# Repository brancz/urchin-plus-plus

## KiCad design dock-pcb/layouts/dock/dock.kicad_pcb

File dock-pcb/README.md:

# dock-pcb

atopile project for the dock board (phase 7), built by the same pipeline as `hardware/`: `scripts/ato_build.sh dock-pcb`.

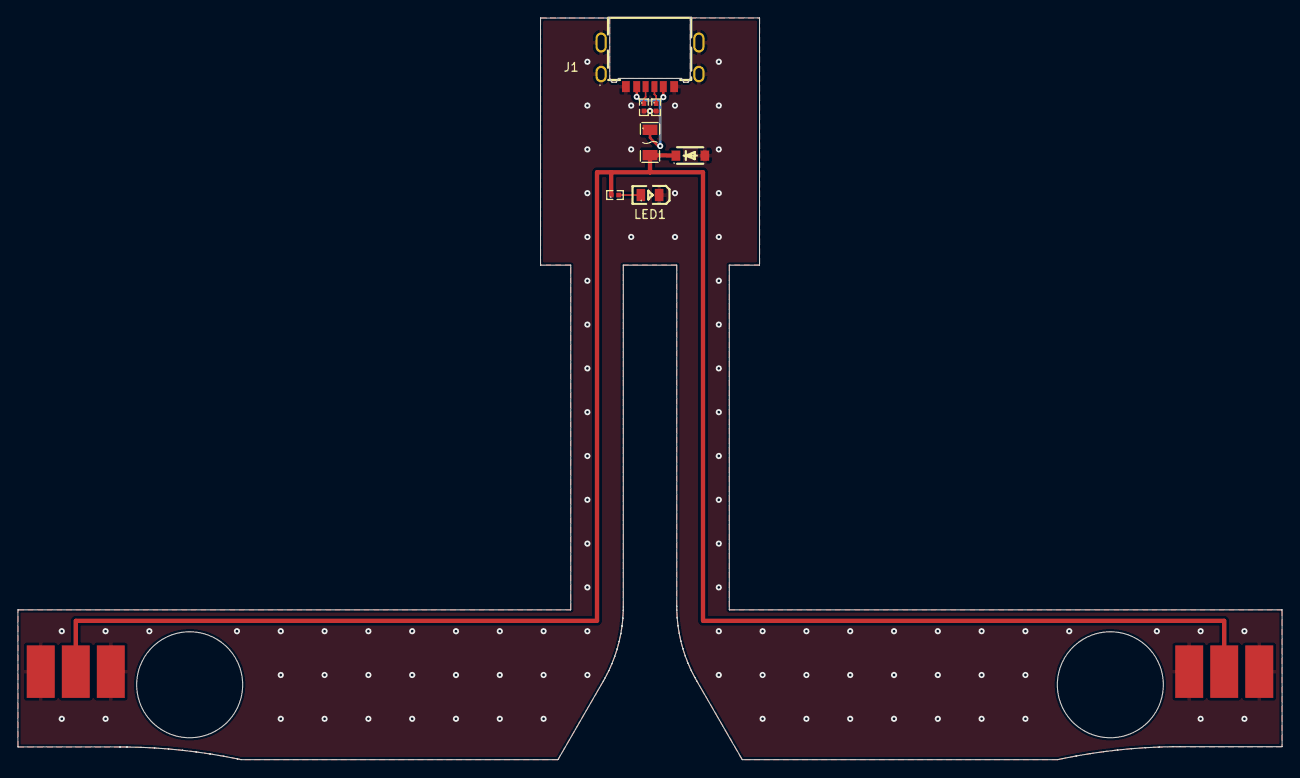
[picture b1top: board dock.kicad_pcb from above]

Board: 2 copper layers, 144.3 x 84.7 mm, 9 parts (0 on the bottom side), 6 nets.

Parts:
D1: SOD-123F_L2.8-W1.8-LS3.7-RD
F1: F1206
J1: TYPE-C-SMD_TYPE-C-31-M-28A
LED1: LED0805-R-RD
R1, R2, R3: R0402
TP1, TP2: DOCK_CONTACTS

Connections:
CC1: J1.A5, R1.1
CC2: J1.B5, R2.1
DOCK_5V: D1.1, F1.2, R3.1, TP1.2, TP2.2
GND: D1.2, J1.7, J1.8, J1.9, J1.10, J1.A12, J1.B12, LED1.2, R1.2, R2.2, TP1.1, TP1.3, TP2.1, TP2.3
LED_A: LED1.1, R3.2
VBUS: F1.1, J1.A9, J1.B9

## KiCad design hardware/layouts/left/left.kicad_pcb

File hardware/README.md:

# hardware

atopile project for the keyboard halves (phase 2 onward): `ato.yaml`, `.ato` sources, `parts/` (generated by `scripts/parts/import_lcsc.py`), and the KiCad layouts for the left and right half under `layouts/`. Build with `scripts/ato_build.sh hardware`, never bare `ato build`.

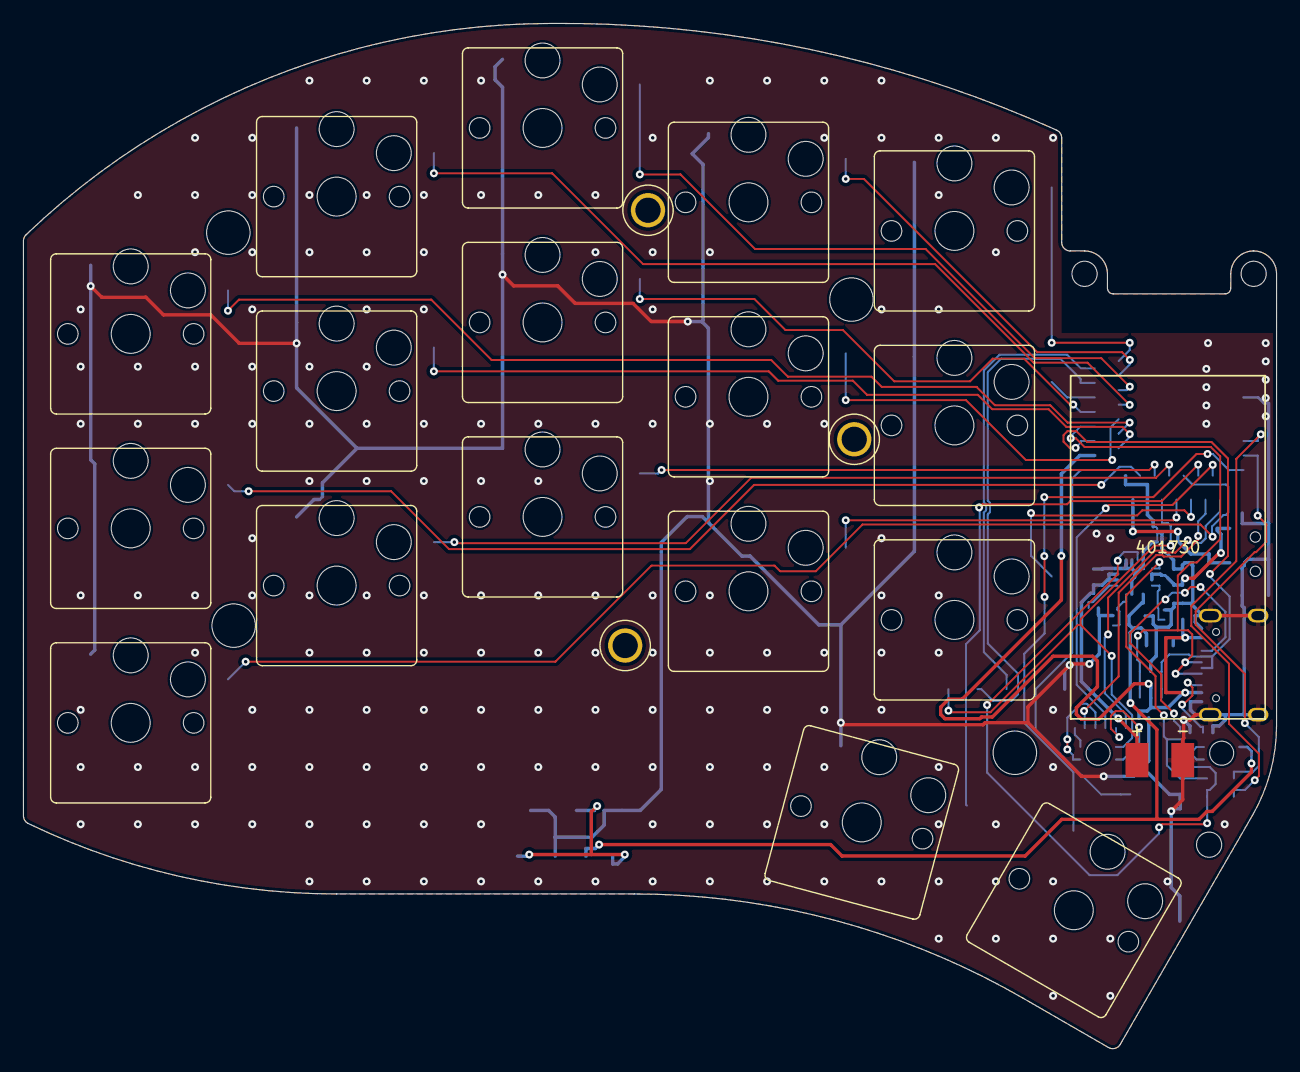
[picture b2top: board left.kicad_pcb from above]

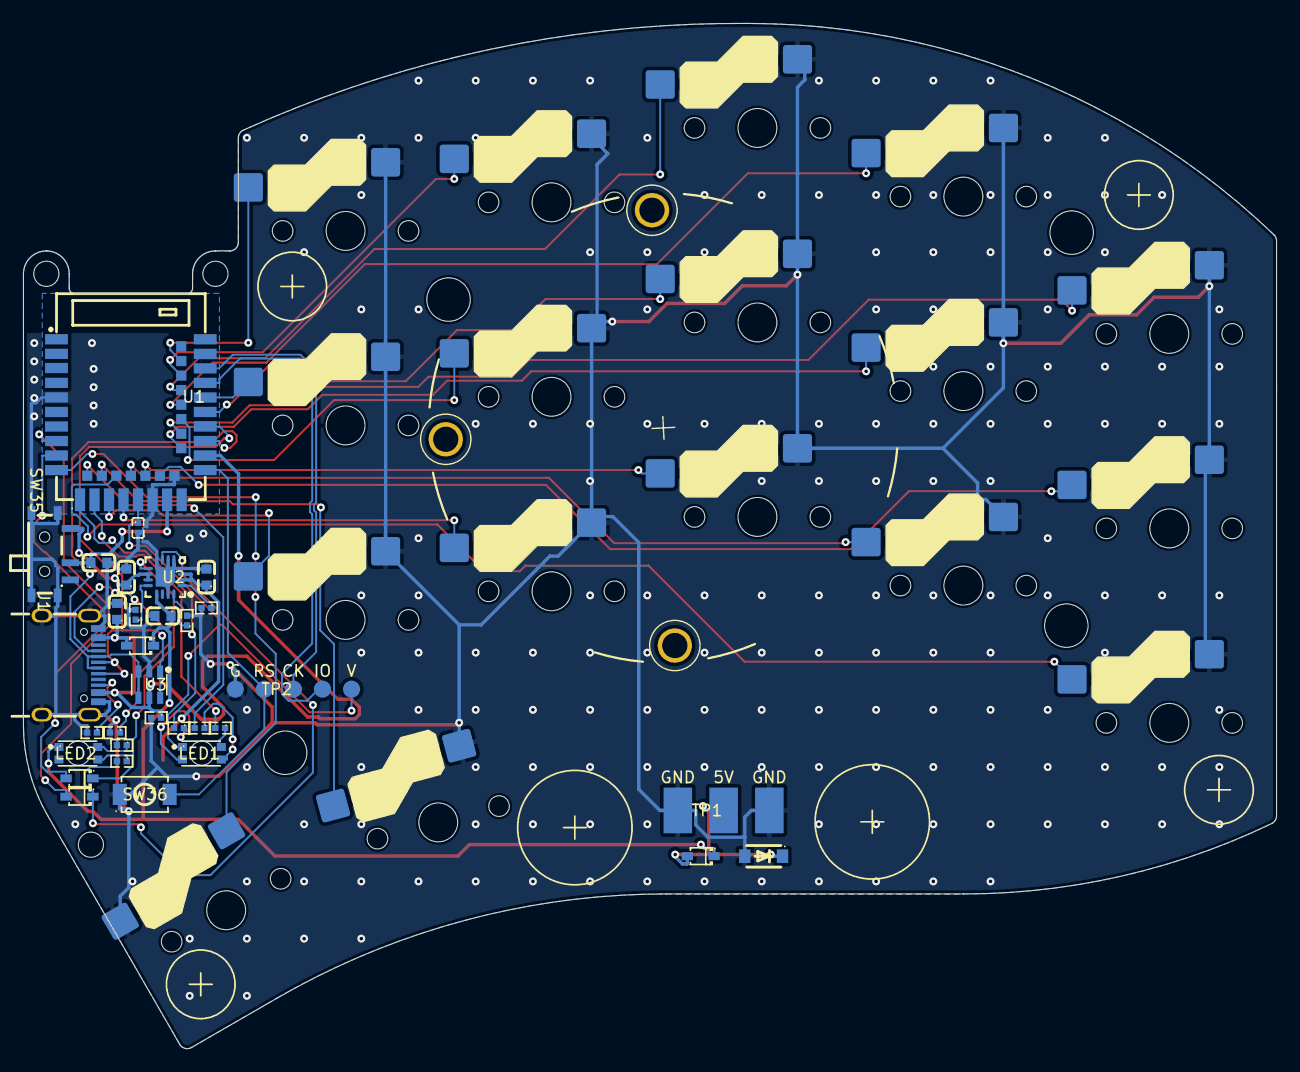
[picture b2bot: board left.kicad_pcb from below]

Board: 2 copper layers, 109.5 x 89.6 mm, 65 parts (38 on the bottom side), 47 nets.

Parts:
BT1: BAT_PADS
BT2: BATTERY_401730
C1: C0402
C2, C3, C4, C5, C6: C0603
D1, D2, D4, D5: SOD-323_L1.8-W1.3-LS2.5-RD
D3: SOD-123F_L2.8-W1.8-LS3.7-RD
H1: Tenting_Puck2_no_pads
H2, H3, H4, H5: M2_hole_4.2mm
H6, H7, H8: M2_hole_3.5mm
J1: USB-C_SMD-TYPE-C-31-M-12_1
LED1, LED2: LED-ARRAY-SMD_1206-4P-L3.2-W1.3-BR-EH
MK1, MK2: STEEL_DISC
MK3, MK4, MK5, MK6: RUBBER_FOOT
R1, R2, R3, R4, R5, R6, R7, R8, R9, R10, R11: R0402
SW1, SW2, SW3, SW4, SW5, SW6, SW7, SW8, SW9, SW10, SW11, SW12, SW13, SW14, SW15, SW16, SW17: SW_Hotswap_Kailh_Choc_V1_tweaked
SW35: SW-TH_MSK12C02
SW36: SW-SMD_L3.9-W3.0-P4.45
TP1: DOCK_PADS
TP2: SWD_PADS
U1: WIRELM-SMD_E73-2G4M08S1C
U2: QFN-16_L3.0-W3.0-P0.50-TL-EP1.7
U3: SOT-23-6_L2.9-W1.6-P0.95-LS2.8-BL

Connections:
CC1: J1.A5, R2.1
CC2: J1.B5, R3.1
CHG_N: D4.1, R6.2, U2.9
CHG_SENSE: D4.2, U1.9
DOCK_5V: D2.2, D3.1, TP1.2
GND: BT1.2, C1.2, C2.2, C3.2, C4.2, C5.2, C6.2, D3.2, J1.1, J1.2, J1.3, J1.4, J1.A1B12, J1.B1A12, R1.2, R2.2, R3.2, R4.2, R5.2, R11.2, SW1.1, SW2.1, SW3.1, SW4.1, SW5.1, SW6.1, SW7.1, SW8.1, SW9.1, SW10.1, SW11.1, SW12.1, SW13.1, SW14.1, SW15.1, SW16.1, SW17.2, SW35.4, SW36.2, TP1.1, TP1.3, TP2.5, U1.5, U1.21, U1.24, U2.4, U2.5, U2.6, U2.8, U2.15, U2.17, U3.2
ILIM: R4.1, U2.12
ISET: R5.1, U2.16
KEY_R0C0: SW1.2, U1.30
KEY_R0C1: SW2.2, U1.34
KEY_R0C2: SW3.2, U1.36
KEY_R0C3: SW4.2, U1.38
KEY_R0C4: SW5.2, U1.40
KEY_R1C0: SW6.2, U1.22
KEY_R1C1: SW7.2, U1.28
KEY_R1C2: SW8.2, U1.33
KEY_R1C3: SW9.2, U1.32
KEY_R1C4: SW10.2, U1.35
KEY_R2C0: SW11.2, U1.16
KEY_R2C1: SW12.2, U1.18
KEY_R2C2: SW13.2, U1.20
KEY_R2C3: SW14.2, U1.17
KEY_R2C4: SW15.2, U1.15
KEY_T0: SW16.2, U1.14
KEY_T1: SW17.1, U1.10
LED_B: R10.2, U1.11
LED_B_K: LED1.2, R10.1
LED_CHG_G: LED2.3, R7.1
LED_CHG_R: LED2.4, R6.1
LED_G: R9.2, U1.12
LED_G_K: LED1.3, R9.1
LED_R: R8.2, U1.13
LED_R_K: LED1.4, R8.1
PGOOD_N: D5.1, R7.2, U2.7
PGOOD_SENSE: D5.2, U1.8
RESET_N: SW36.1, TP2.4, U1.26
SWDCLK: TP2.3, U1.39
SWDIO: TP2.2, U1.37
TS: R1.1, U2.1
USB_DN: J1.A7, J1.B7, U1.29, U3.3, U3.4
USB_DP: J1.A6, J1.B6, U1.31, U3.1, U3.6
VBAT: BT1.1, C4.1, U2.2, U2.3
VBUS: C5.1, D1.2, J1.A4B9, J1.B4A9, R11.1, U1.27, U3.5
VDD: C1.1, LED1.1, TP2.1, U1.19
VDDH: C6.1, SW35.2, U1.23
VIN: C2.1, D1.1, D2.1, LED2.1, U2.13
VSYS: C3.1, SW35.1, U2.10, U2.11

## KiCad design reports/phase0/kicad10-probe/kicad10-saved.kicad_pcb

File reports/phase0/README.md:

# Phase 0 — toolchain proof

Dates: 2026-10-17 to 2026-10-18. Machine: macOS (arm64), bash 3.2. CI: GitHub Actions in the `kicad/kicad:9.0.9` image (Linux, bash 5), plus a macOS syntax job.

## Exit criteria

| Criterion (docs/PLAN.md) | Result | Evidence |
|---|---|---|
| Clean round-trip report | **KiCad 10.0.7: fails.** atopile can't rebuild a board KiCad 10 has saved. **KiCad 9.0.9** (the documented fallback): all 12 steps pass, locally and in CI | `kicad10-probe/`, `roundtrip/` |
| CI green on an empty build | green: run 39119942514 | see "CI" |
| Exact tool versions and Freerouting checksum in SETUP.md | recorded; `scripts/checks/toolchain.sh --local` passes, including the frozen dependency trees | `docs/SETUP.md`, `toolchain.env`, `constraints/`, `roundtrip/toolchain.txt` |
| Repo layout, `.gitignore`, CI skeleton | done | repo root, `.github/workflows/ci.yml` |
| Reviewer pass | two rounds; every finding fixed or dispositioned | `review.md` |

## Round-trip (`scripts/roundtrip/run.sh`, also run in CI)

The fixture (`scripts/roundtrip/fixture/`) is a two-resistor divider and a decoupling capacitor (LCSC C25744, C1525), both with bottom-side footprints as rule 2 requires, plus a mechanical M2 hole on the top. It is built in a throwaway git repo, and every build goes through `scripts/ato_build.sh`, the same wrapper the real boards use.

| Step | What it proves | Result |
|---|---|---|
| 1 build | first build through the wrapper | 4 footprints, format 20241229 |
| 2 pcbnew edit | JLC-like design rules, an outline, moves and rotations (one at 15°), B.Cu tracks, a via, a two-layer GND zone, the hole placed; saved by KiCad 9 | DRC 0 errors, 0 unconnected |
| 3 rebuild | every edit survives: `board_diff --strict` (empty semantic diff, identical canonical pcbnew serialization) | pass; DRC identical to step 2 |
| 4 idempotent | a second rebuild and `ato build --frozen` change nothing | pass |
| 5 add a part | exactly one footprint added, nothing else changes | pass, after `fix_stale_nets` put back 3 copper items that atopile left off their nets |
| 6 stable | rebuild and `--frozen` change nothing after the new part is placed | pass |
| 7 uncommitted save | net churn, then a pcbnew save without a commit (KiCad renumbers nets), then a rebuild: a free MID via stays MID | pass |
| 8 rename | net MID → MIDPOINT in the circuit: copper follows, and board_diff reports a rename | pass |
| 9 refused | a footprint atopile didn't create, a footprint flipped against its library side, and a locked footprint are each refused before atopile runs, and the board is left untouched | pass |
| 10 board history | `board_history.sh` over the repo's commits; a commit that drops a track fails unless its message allows it; merge commits are skipped | pass |
| 11 Freerouting | rip up, DSN export, Freerouting 2.5.0, SES import | DRC 0 errors, 0 unconnected |
| 12 KiKit | `kikit fab jlcpcb` | 16 Gerber/drill files |

DRC reports warnings only: `silk_overlap` and `silk_over_copper` from the easyeda2kicad footprints' own silkscreen (F5).

## KiCad 10 probe (`scripts/roundtrip/kicad10_probe.sh`)

atopile builds the fixture, and KiCad 10.0.7's pcbnew edits and saves it (format 20260206). The next `ato build` fails with `UnexpectedType in kicad.pcb.Layer field 'tenting'`, both with atopile 0.15.7 and with 0.15.9, the last CLI release. KiCad 10 writes `(tenting (front yes) (back yes))` into every board's setup, so every KiCad 10-saved board is affected.

## Findings about the toolchain

| # | Finding | Disposition |
|---|---|---|
| F1 | atopile (0.15.7 and 0.15.9) can't read any board saved by KiCad 10. | KiCad 9.0.9 per the fallback, installed side by side at `/Applications/KiCad9`. The guardrail rejects KiCad files newer than KiCad 9's formats, and every KiCad-using script checks the version first. |
| F2 | atopile's part server is gone: NXDOMAIN since about 2026-07-18 (atopile#1829). 0.15.8+ needs a login to a legacy endpoint (HTTP 401 without one), and the CLI is end-of-life (`upstream-checks.txt`). | All parts are local atomic parts from `scripts/parts/import_lcsc.py`, so builds are offline. Stay on 0.15.7, with its dependency tree frozen in `constraints/`. |
| F3 | atopile re-creates a net under a new number when fewer than 80% of its pads already carry its name, and leaves that net's tracks, vias, and zones behind: on macOS on the old, now meaningless number; on Linux on net 0. KiCad recomputes the net of copper that touches a pad on load, but free copper (stitching vias, stubs) and zones (resolved by `net_name`) end up on the wrong net or none. | `scripts/fix_stale_nets.py` matches each copper item by UUID to the pre-build snapshot. It keeps net numbers atopile kept (including in-place renames) and restores the rest by name. Steps 5, 7, and 8, on both platforms. |
| F4 | atopile deletes every footprint it didn't create. | Every footprint is an atopile part, mechanical ones too (atomic part, explicit `has_designator`, `exclude_from_bom`/`exclude_from_pos_files`). The guardrail refuses footprints that don't resolve to a library. Steps 2 and 9. |
| F5 | easyeda2kicad footprints draw silkscreen over their own pads. | Open item for phase 2: check each footprint against its datasheet land pattern. |
| F6 | atopile re-syncs every footprint from its library on each build and matches items by geometry only, so two items with the same geometry on different layers get merged (here an F.CrtYd circle became B.CrtYd). | The guardrail rejects such footprints. `board_diff --mode build` fails if an existing footprint's graphics, pads, attributes, or field placement change while its library footprint doesn't. |
| F7 | `kicad-cli fp/sym upgrade` writes files in its own KiCad version's format. | The importer refuses a `kicad-cli` that isn't the pinned version, and the guardrail checks every `.kicad_mod`/`.kicad_sym`. |
| F8 | `has_datasheet` makes `ato build` download the URL, and LCSC's is a product page. | The importer doesn't emit it. Datasheets go in `docs/datasheets/`. |
| F9 | Instance net-name traits on `ElectricPower.hv/lv` are ignored. | Open item for phase 2: name rails on plain signals. |
| F10 | KiKit's `fab jlcpcb --assembly` needs a schematic, and atopile produces none. | Open item for phase 6: BOM from atopile, CPL from `kicad-cli pcb export pos`. |
| F11 | atopile flips each footprint to its library's side and back on every build. For a front-side library footprint placed on the bottom, the flip corrupts text rotations on every build (permanent `--frozen` failure). | Bottom-side parts get bottom-side library footprints (`footprint_to_bottom.py`, the importer's default), and the guardrail refuses a footprint on the other side from its library. Steps 2–6 at 15° and 270°, plus the step 9 refusal. |
| F12 | atopile drops whatever its data model lacks: locks on footprints, tracks, and zones; zones inside footprints; `fp_curve`; text boxes; groups; extra zone outlines. | The guardrail mirrors atopile's model (`pcb.zig`) and refuses such content before building. Keep-outs, including the antenna keep-out (rule 6), are board-level rule areas. Step 9 (lock). |

## CI

Green: https://github.com/brancz/urchin-plus-plus/actions/runs/39119942514 (commit 6c2ccd6). In that run:

- toolchain check OK, and all 137 installed atopile/KiKit packages are pinned
- the 12-step round-trip passes on Linux
- the guardrails pass on the committed KiCad files
- board history is OK (no design boards yet)
- the macOS job parses every script with bash 3.2 and compiles them with Python 3.9
- the dock environment installs from its lockfile

Earlier runs failed twice, and both failures led to fixes. In the first, the round-trip failed at step 5 on Linux, which is how F3's platform difference was found. In the second, the guardrail correctly rejected the KiCad 10 evidence board under `reports/`.

The second review round's fixes were checked against the reviewer's repro scripts and are covered by the round-trip. They have not been re-reviewed independently.

## Reproduce

```bash
scripts/checks/toolchain.sh --local
scripts/roundtrip/run.sh scratch/roundtrip reports/phase0/roundtrip
scripts/roundtrip/kicad10_probe.sh /Applications/KiCad/KiCad.app reports/phase0/kicad10-probe
scripts/roundtrip/upstream_checks.sh > reports/phase0/upstream-checks.txt
```

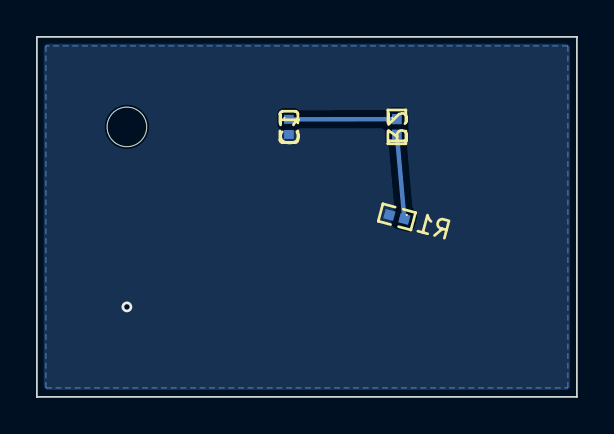
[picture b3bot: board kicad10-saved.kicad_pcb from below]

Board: 2 copper layers, 30.0 x 20.0 mm, 4 parts (3 on the bottom side), 3 nets.

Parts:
C1: C0402
H1: MountingHole_2.2mm_M2
R1, R2: R0402

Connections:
GND: C1.2, R1.2
MID: R1.1, R2.2
VCC: C1.1, R2.1

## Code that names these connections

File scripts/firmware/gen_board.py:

#!/usr/bin/env python3
"""Generate the ZMK board's pin and layout devicetree from the hardware sources (phase 8).

    python3 scripts/firmware/gen_board.py [--check]

The LED outputs are open-drain: they only ever pull a cathode low. Each half's LED pins
are key inputs on the other half, so a half flashed with the other half's image must not
drive them high against a pressed key's short to ground.

Writes, into firmware/boards/urchin_pp/:
  urchin_pp_left-pins.dtsi, urchin_pp_right-pins.dtsi
      each half's direct-wired key GPIOs (kscan input order r0c0..r0c4, r1c0..r1c4,
      r2c0..r2c4, t0, t1), its status LED's red/green/blue GPIOs and the charger's
      PGOOD/CHG sense GPIOs, from hardware/pinmap.json (scripts/circuit/gen_halves.py).
  urchin_pp-layouts.dtsi
      the matrix transform (34 keymap positions; the right half's kscan columns are
      offset by 17) and ZMK's physical layout for ZMK Studio, with every key at its
      switch position and rotation from hardware/geometry/urchin.json (rule 1's source).

Keymap positions: three rows of 5 + 5 keys, then the thumbs. Row by row, left half
c0 (outer pinky) to c4 (index), right half c4 (index) to c0 (outer pinky); thumbs left
t0, left t1 (inner), right t1 (inner), right t0. The right half's signals are mirrored
names (gen_halves.py), so its c0 is its outer pinky column.

Layout units: 1 key unit = 18 mm, the Urchin's column pitch; rows are 17 mm apart, so
keys are 100 x 94 centi-units. ZMK's rotation is clockwise-positive, KiCad's
counter-clockwise-positive. Each half must use every key and function exactly once, no
GPIO twice, and not P0.18 (reset) or P0.09/P0.10 (NFC). --check fails if any generated
file differs. Python 3.9.
"""

import argparse
import json
import sys
from pathlib import Path

ROOT = Path(__file__).resolve().parents[2]
BOARD_DIR = ROOT / "firmware/boards/urchin_pp"
KEY_ORDER = ["r%dc%d" % (r, c) for r in range(3) for c in range(5)] + ["t0", "t1"]
HALF_KEYS = len(KEY_ORDER)  # 17: the right half's kscan columns are offset by this
UNIT_MM = 18.0
KEY_W, KEY_H = 100, 94
GAP_UNITS = 150  # between the halves in the physical layout
HEADER = "/* Generated by scripts/firmware/gen_board.py from %s. Do not edit. */\n"


def gpio(name):
    """'P0_17' -> ('gpio0', 17)"""
    port, pin = name[1:].split("_")
    return "gpio%d" % int(port), int(pin)


def keymap_positions():
    """[(half, signal)] in keymap order."""
    out = []
    for r in range(3):
        out += [("left", "r%dc%d" % (r, c)) for c in range(5)]
        out += [("right", "r%dc%d" % (r, c)) for c in reversed(range(5))]
    return out + [("left", "t0"), ("left", "t1"), ("right", "t1"), ("right", "t0")]


RESERVED = {"P0_18": "reset", "P0_09": "NFC1", "P0_10": "NFC2"}
FUNCTIONS = ("led_r", "led_g", "led_b", "pgood_sense", "chg_sense")


def validate(half, rows):
    """Every key and function exactly once, no GPIO twice, no reserved pin."""
    signals = [r["signal"] for r in rows]
    missing = sorted((set(KEY_ORDER) | set(FUNCTIONS)) - set(signals))
    dupes = sorted({g for g in (r["gpio"] for r in rows) if [x["gpio"] for x in rows].count(g) > 1})
    reserved = sorted("%s (%s)" % (r["gpio"], RESERVED[r["gpio"]]) for r in rows if r["gpio"] in RESERVED)
    problems = (["missing %s" % ", ".join(missing)] if missing else []) + \
               (["GPIO used twice: %s" % ", ".join(dupes)] if dupes else []) + \
               (["reserved pin used: %s" % ", ".join(reserved)] if reserved else [])
    if problems:
        sys.exit("gen_board: %s half: %s" % (half, "; ".join(problems)))


def pins_dtsi(half, rows):
    validate(half, rows)
    by_signal = {r["signal"]: r for r in rows}
    lines = [HEADER % "hardware/pinmap.json", "&kscan0 {", "    input-gpios"]
    for i, sig in enumerate(KEY_ORDER):
        r = by_signal[sig]
        port, pin = gpio(r["gpio"])
        lines.append("        %s <&%s %d (GPIO_ACTIVE_LOW | GPIO_PULL_UP)>  /* %d: %s %s, module pin %d */" % (
            "=" if i == 0 else ",", port, pin, i, sig, r["ref"], r["module_pin"]))
    lines += ["        ;", "};", ""]
    for label, sig in (("led_red", "led_r"), ("led_green", "led_g"), ("led_blue", "led_b")):
        port, pin = gpio(by_signal[sig]["gpio"])
        lines.append("&%s { gpios = <&%s %d (GPIO_ACTIVE_LOW | GPIO_OPEN_DRAIN)>; };  /* status LED cathode, module pin %d */" % (
            label, port, pin, by_signal[sig]["module_pin"]))
    lines += ["", "&battery {"]
    for prop, sig in (("power-good-gpios", "pgood_sense"), ("charging-gpios", "chg_sense")):
        port, pin = gpio(by_signal[sig]["gpio"])
        lines.append("    %s = <&%s %d (GPIO_ACTIVE_LOW | GPIO_PULL_UP)>;  /* %s, module pin %d */" % (
            prop, port, pin, sig, by_signal[sig]["module_pin"]))
    lines.append("};")
    if half == "right":
        lines += ["", "&default_transform {", "    col-offset = <%d>;" % HALF_KEYS, "};"]
    return "\n".join(lines) + "\n"


def layouts_dtsi(pinmap, geometry):
    refs = {half: {r["signal"]: r["ref"] for r in rows if r["kind"] == "key"} for half, rows in pinmap.items()}
    switches = {half: {s["ref"]: s for s in geometry[half]["switches"]} for half in pinmap}
    # place the left half first, then the right half to its right (KiCad has them the other way round)
    xs = {half: [switches[half][ref]["x"] for ref in refs[half].values()] for half in pinmap}
    ys = [switches[h][ref]["y"] for h in pinmap for ref in refs[h].values()]
    left_w = (max(xs["left"]) - min(xs["left"])) / UNIT_MM * 100
    origin = {"left": min(xs["left"]), "right": min(xs["right"])}
    offset = {"left": KEY_W / 2, "right": KEY_W / 2 + left_w + GAP_UNITS}
    y0 = min(ys)

    transform, keys = [], []
    for half, sig in keymap_positions():
        col = KEY_ORDER.index(sig) + (HALF_KEYS if half == "right" else 0)
        transform.append("RC(0,%d)" % col)
        sw = switches[half][refs[half][sig]]
        cx = offset[half] + (sw["x"] - origin[half]) / UNIT_MM * 100
        cy = KEY_H / 2 + (sw["y"] - y0) / UNIT_MM * 100
        rot = int(round(-sw["rot"] * 100))  # ZMK: clockwise-positive centi-degrees
        keys.append((KEY_W, KEY_H, int(round(cx - KEY_W / 2)), int(round(cy - KEY_H / 2)), rot,
                     int(round(cx)), int(round(cy)), half, sig, sw["ref"]))
    num = lambda v: "(%d)" % v if v < 0 else "%d" % v
    lines = [HEADER % "hardware/pinmap.json and hardware/geometry/urchin.json",
             "#include <physical_layouts.dtsi>", "", "/ {",
             "    default_transform: keymap_transform_0 {",
             "        compatible = \"zmk,matrix-transform\";",
             "        rows = <1>;",
             "        columns = <%d>;" % (2 * HALF_KEYS),
             "        map = <"]
    for i in range(0, 30, 10):
        lines.append("            " + " ".join(transform[i:i + 10]))
    lines += ["            " + " ".join(transform[30:]), "        >;", "    };", "",
              "    physical_layout0: physical_layout_0 {",
              "        compatible = \"zmk,physical-layout\";",
              "        display-name = \"urchin++\";",
              "        transform = <&default_transform>;",
              "        keys  //                     w   h     x    y      rot    rx    ry"]
    for i, (w, h, x, y, r, rx, ry, half, sig, ref) in enumerate(keys):
        lines.append("            %s <&key_physical_attrs %3d %3d %5d %4d %8s %5d %5d>  /* %d: %s %s %s */" % (
            "=" if i == 0 else ",", w, h, x, y, num(r), rx, ry, i, half, sig, ref))
    lines += ["            ;", "    };", "};"]
    return "\n".join(lines) + "\n"


def main():
    ap = argparse.ArgumentParser(description=__doc__, formatter_class=argparse.RawDescriptionHelpFormatter)
    ap.add_argument("--check", action="store_true")
    args = ap.parse_args()
    pinmap = json.loads((ROOT / "hardware/pinmap.json").read_text())["halves"]
    geometry = json.loads((ROOT / "hardware/geometry/urchin.json").read_text())["halves"]
    files = {"urchin_pp_%s-pins.dtsi" % half: pins_dtsi(half, rows) for half, rows in pinmap.items()}
    files["urchin_pp-layouts.dtsi"] = layouts_dtsi(pinmap, geometry)
    stale = []
    for name, text in sorted(files.items()):
        path = BOARD_DIR / name
        if args.check:
            if not path.exists() or path.read_text() != text:
                stale.append(name)
        else:
            path.parent.mkdir(parents=True, exist_ok=True)
            path.write_text(text)
    if args.check:
        print("gen_board: %s" % ("OK" if not stale else "FAIL, stale: " + ", ".join(stale)))
        sys.exit(1 if stale else 0)
    print("gen_board: wrote %s" % ", ".join(sorted(files)))


if __name__ == "__main__":
    main()
